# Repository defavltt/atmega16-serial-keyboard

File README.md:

# ATmega16 serial keyboard

## Features

 - Key macros can be added in code
 
 - Caps toggle with LED indication
 
 - Select 115200 serial baud rate at power up (9600 default)
 
 - Send values outside ASCII range with non letter keys
 
 - Works with laptop mini keyboards 26-pin (28-pin with 2 being a short)

## Operation

When powering up, while the LED is lit, you can choose either: 9600 baud by not pressing DEL or 115200 by pressing DEL. After that you can choose a macro key mapping preset with F1 - F12. Finally when the LED is off you can start typing.

Toggling caps lock is done by a single press on the caps key. Shift key inverts it. When caps is on, the numbers change into symbols too.

_When designing an application at the other end of the serial cable, you may consider to take advantage of the non letter keys that send values (>200), as interface navigation. For example: ESC to exit out of options, HOME to exit out to start screen, ENTER to send a message or save an option, arrow keys for navigating through options and F1 - F12 for predefined functions._

# Hardware

Can be made with ATmega16/164/32/324/644/1284/8535 (44pin TQFP packege).

For 115200 serial baud rate a 16Mhz or a different suitable crystal is required, even though it's not included in the board design.
Board is designed for single side etching and some wire jumpers, vias are only for ground connection to the bottom layer. Feel free to improve it.

There are pads left on the PCB for ISP programming.

File for a 3D printed case is included. This case only suits keyboards with frame size - 211mm x 80mm.

_values that can be sent from the corresponding keys_

_assembled board only with components, no jumper wires or crystal_

_< toner layer to protect copper from etchant | etched pcb >_

_serial keyboard connected to a RFM95 LoRa communicator_

_keyboard ribbon cable pin multiplexing mapping_

# Programming

 - Download and install [MightyCore](https://github.com/MCUdude/MightyCore)
 
 - Open code in IDE of choice
 
 - Configure board settings
 
   - Select your MCU and crystal frequency
   
   - Leave the rest of the board settings by default
   
   - If want, you can enable bootloader and leave out a reset pin on the serial connector for future configuring of the key macros.
   
 - Flash via ISP programmer and it's done.

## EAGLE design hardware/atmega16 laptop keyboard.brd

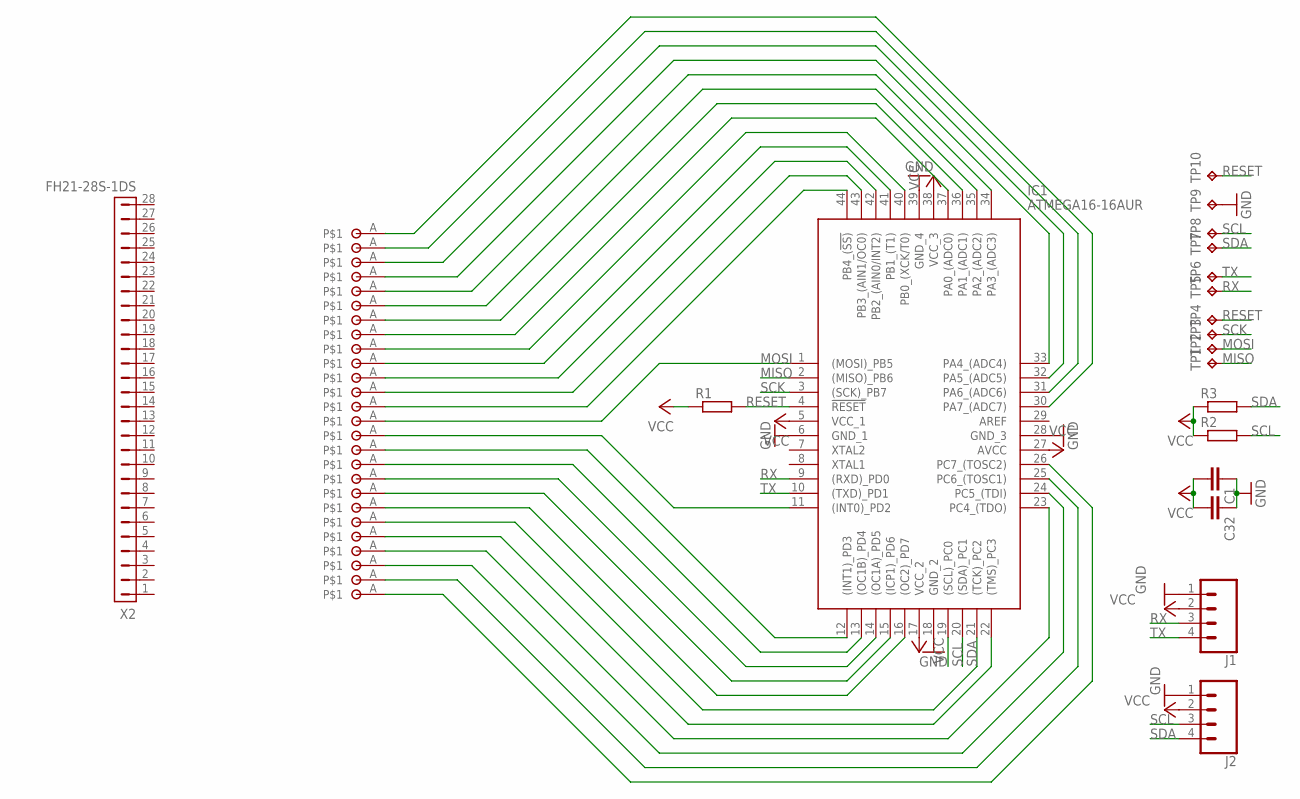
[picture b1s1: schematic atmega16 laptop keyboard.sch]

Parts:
C1, C32: C-EUC0805; C0805
IC1: ATMEGA16-16AUR; QFP80P1200X1200X120-44N
J1, J2: CONN_04LONGPADS; 1X04_LONGPADS
R1, R2, R3: R-EU_M0805; M0805
TP1, TP2, TP3, TP4, TP5, TP6, TP7, TP8, TP9, TP10: TPTP15R; TP15R
U$1, U$2, U$3, U$4, U$5, U$6, U$7, U$8, U$9, U$10, U$11, U$12, U$13, U$14, U$15, U$16, U$17, U$18, U$19, U$20, U$21, U$22, U$23, U$24, U$25, U$26: PAD1
X2: FH21-28S-1DS

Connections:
GND: C1.1, C32.1, IC1.6 (GND_1), IC1.18 (GND_2), IC1.28 (GND_3), IC1.39 (GND_4), J1.1, J2.1, TP9.TP
MISO: IC1.2 ((MISO)_PB6), TP1.TP
MOSI: IC1.1 ((MOSI)_PB5), TP2.TP, U$14.A
unnamed: IC1.11 ((INT0)_PD2), U$15.A
unnamed: IC1.12 ((INT1)_PD3), U$16.A
unnamed: IC1.13 ((OC1B)_PD4), U$17.A
unnamed: IC1.14 ((OC1A)_PD5), U$18.A
unnamed: IC1.15 ((ICP1)_PD6), U$19.A
unnamed: IC1.16 ((OC2)_PD7), U$20.A
unnamed: IC1.21 ((TCK)_PC2), U$21.A
unnamed: IC1.22 ((TMS)_PC3), U$22.A
unnamed: IC1.23 (PC4_(TDO)), U$23.A
unnamed: IC1.24 (PC5_(TDI)), U$24.A
unnamed: IC1.25 (PC6_(TOSC1)), U$25.A
unnamed: IC1.26 (PC7_(TOSC2)), U$26.A
unnamed: IC1.44 (PB4_(!SS)), U$13.A
unnamed: IC1.43 (PB3_(AIN1/OC0)), U$12.A
unnamed: IC1.42 (PB2_(AIN0/INT2)), U$11.A
unnamed: IC1.41 (PB1_(T1)), U$10.A
unnamed: IC1.40 (PB0_(XCK/T0)), U$9.A
unnamed: IC1.37 (PA0_(ADC0)), U$8.A
unnamed: IC1.36 (PA1_(ADC1)), U$7.A
unnamed: IC1.35 (PA2_(ADC2)), U$6.A
unnamed: IC1.34 (PA3_(ADC3)), U$5.A
unnamed: IC1.33 (PA4_(ADC4)), U$4.A
unnamed: IC1.32 (PA5_(ADC5)), U$3.A
unnamed: IC1.31 (PA6_(ADC6)), U$2.A
unnamed: IC1.30 (PA7_(ADC7)), U$1.A
RESET: IC1.4 (!RESET), R1.2, TP4.TP, TP10.TP
RX: IC1.9 ((RXD)_PD0), J1.3, TP5.TP
SCK: IC1.3 ((SCK)_PB7), TP3.TP
SCL: IC1.19 ((SCL)_PC0), J2.3, R2.2, TP8.TP
SDA: IC1.20 ((SDA)_PC1), J2.4, R3.2, TP7.TP
TX: IC1.10 ((TXD)_PD1), J1.4, TP6.TP
VCC: C1.2, C32.2, IC1.5 (VCC_1), IC1.17 (VCC_2), IC1.27 (AVCC), IC1.38 (VCC_3), J1.2, J2.2, R1.1, R2.1, R3.1

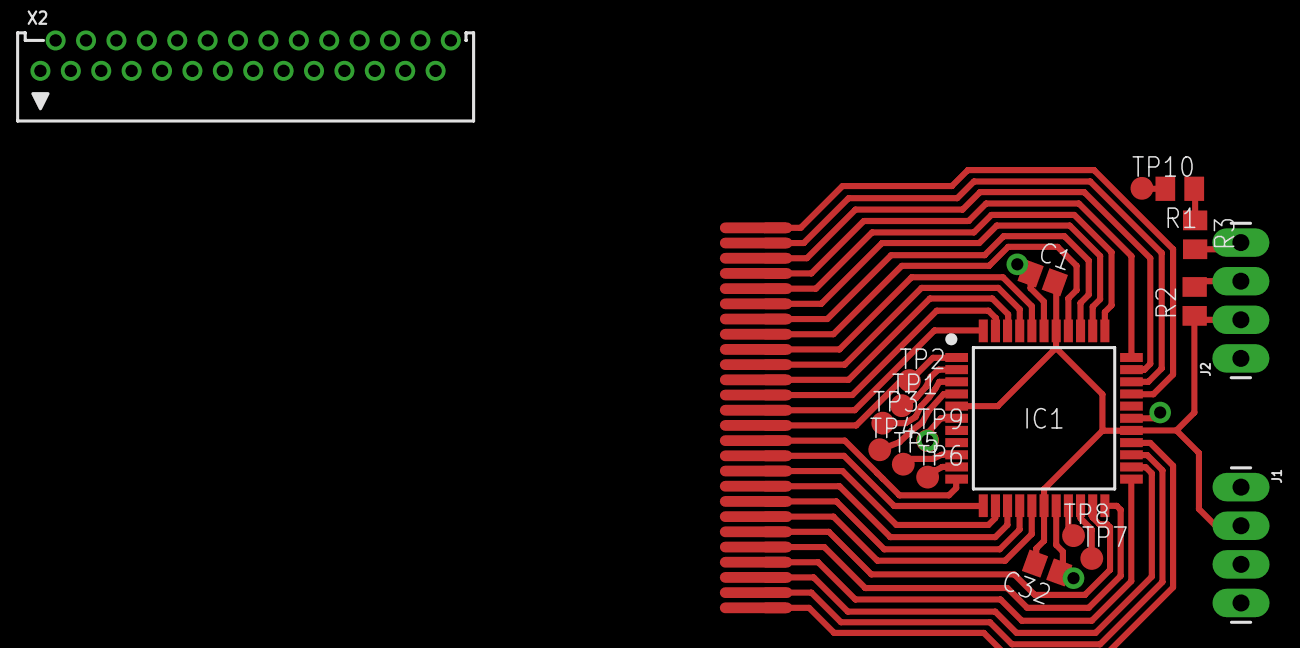
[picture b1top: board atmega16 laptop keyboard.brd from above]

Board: 2 copper layers, 45 parts (0 on the bottom side), 35 nets.

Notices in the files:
parts and their libraries:
SparkFun-Connectors: Licensing: Creative Commons ShareAlike 4.0 International - https://creativecommons.org/licenses/by-sa/4.0
